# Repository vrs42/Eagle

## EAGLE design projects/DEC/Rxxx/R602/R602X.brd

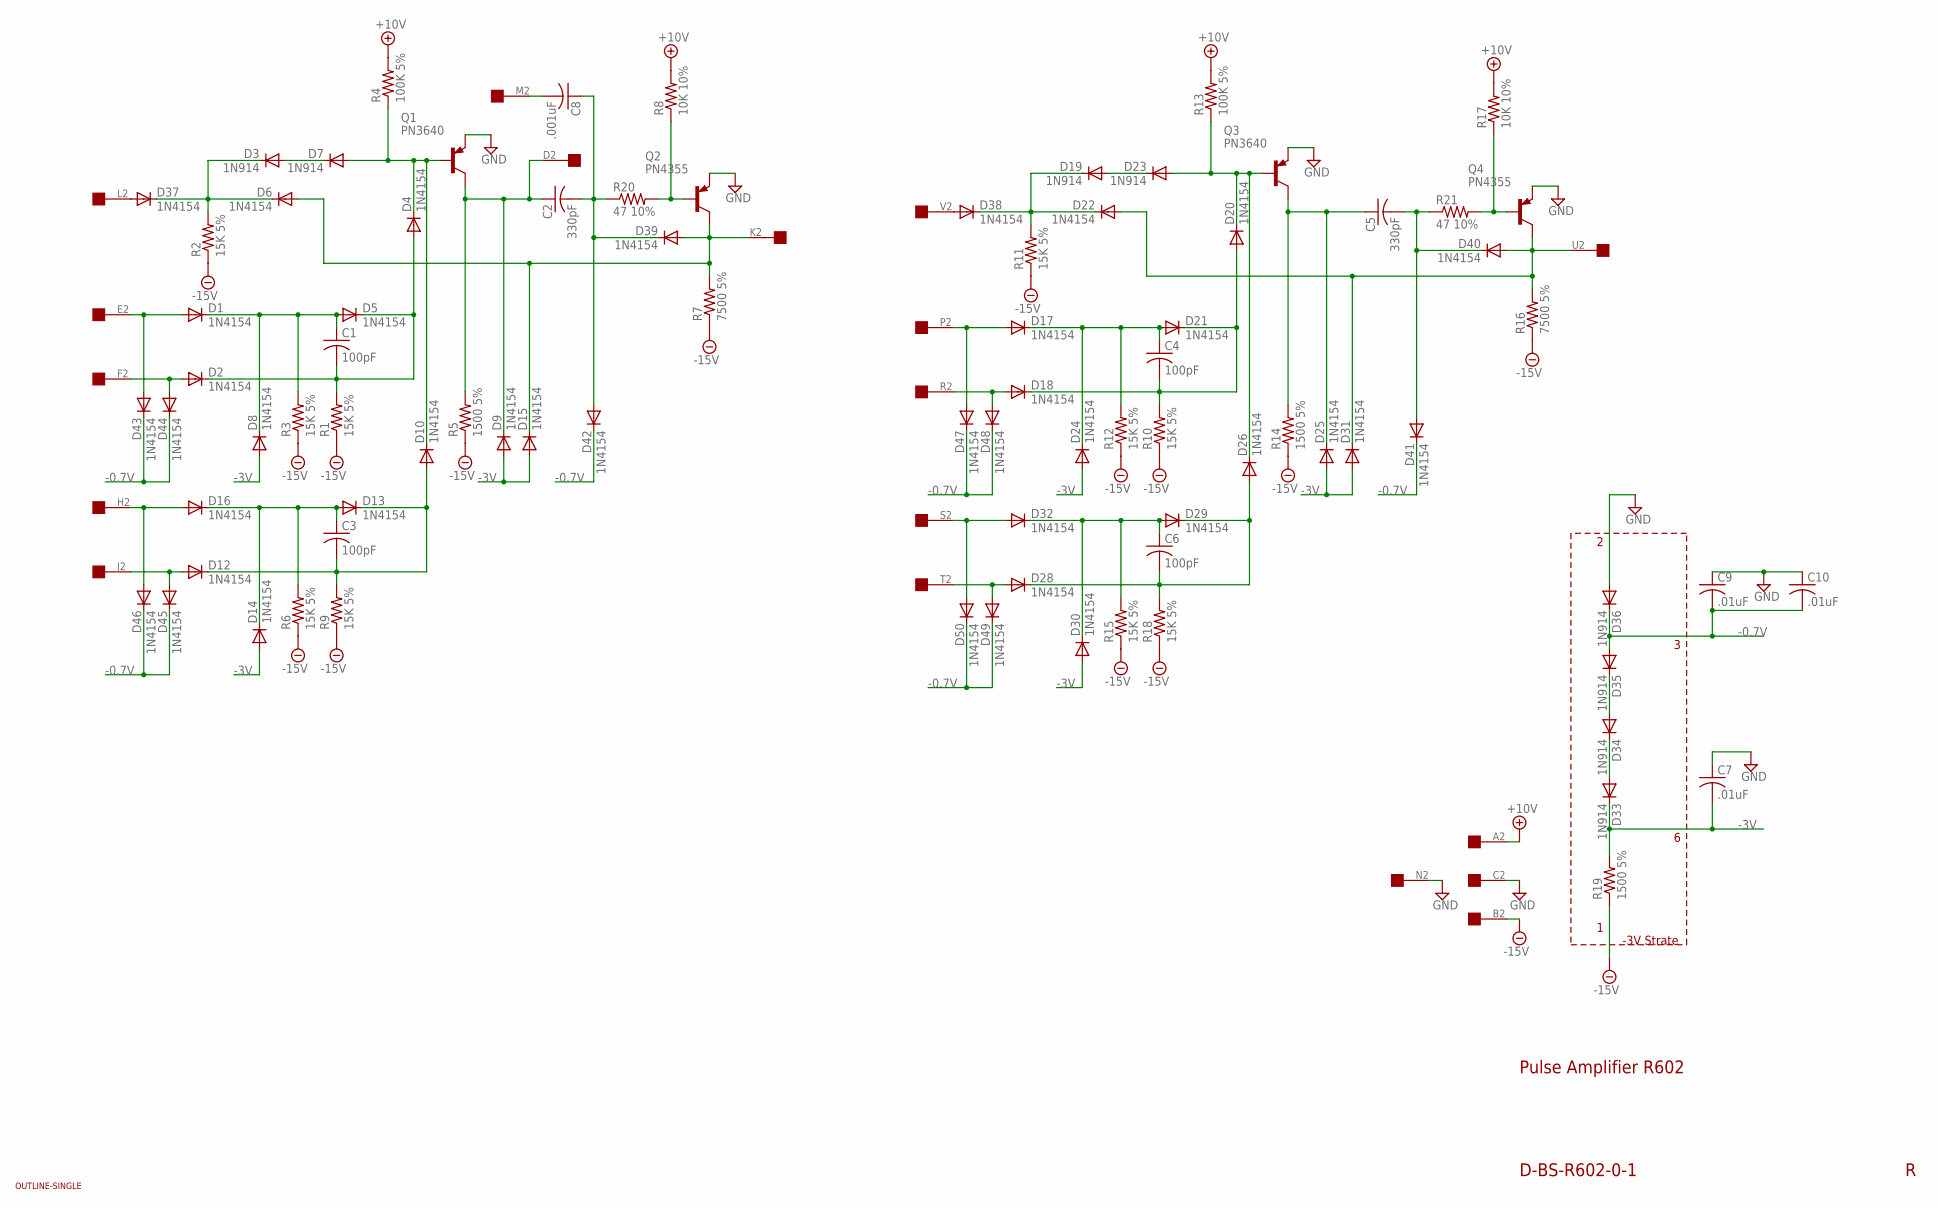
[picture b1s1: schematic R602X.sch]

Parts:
C1, C3, C4, C6: 100pF; C050-025X075
C2, C5: 330pF; C050-025X075
C7: .01uF; C075-032X103
C8: .001uF; C050-025X075
C9, C10: .01uF; C050-025X075
D1, D2, D4, D5, D6, D8, D9, D10, D12, D13, D14, D15, D16, D17, D18, D20, D21, D22, D24, D25, D26, D28, D29, D30, D31, D32, D37, D38, D39, D40, D41, D42, D43, D44, D45, D46, D47, D48, D49, D50: 1N4154; DO35-10
D3, D7, D19, D23, D33, D34, D35, D36: 1N914; DO35-10
Q1, Q3: PN3640; TO39
Q2, Q4: PN4355; TO39
R1, R2, R3, R6, R9, R10, R11, R12, R15, R18: 15K 5%; 0207/10
R4, R13: 100K 5%; 0207/10
R5, R14, R19: 1500 5%; 0207/10
R7, R16: 7500 5%; 0207/10
R8, R17: 10K 10%; 0207/10
R20, R21: 47 10%; 0207/10
U$1: OUTLINE-SINGLE; SINGLE
U$2: EDGE-1; EDGE-CON1

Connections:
+10V: R4.2, R8.2, R13.2, R17.2, U$2.A2
-0.7V: C9.2, C10.2, D35.A, D36.C, D41.C, D42.C, D43.C, D44.C, D45.C, D46.C, D47.C, D48.C, D49.C, D50.C
-3V: C7.2, D8.A, D9.A, D14.A, D15.A, D24.A, D25.A, D30.A, D31.A, D33.C, R19.2
-15V: R1.1, R2.1, R3.1, R5.1, R6.1, R7.1, R9.1, R10.1, R11.1, R12.1, R14.1, R15.1, R16.1, R18.1, R19.1, U$2.B2
GND: C7.1, C9.1, C10.1, D36.A, Q1.1 (E), Q2.1 (E), Q3.1 (E), Q4.1 (E), U$2.C2, U$2.N2
unnamed: D37.A, U$2.L2
unnamed: D3.C, D6.C, D37.C, R2.2
unnamed: D1.A, D43.A, U$2.E2
unnamed: D2.A, D44.A, U$2.F2
unnamed: C1.1, D1.C, D5.A, D8.C, R3.2
unnamed: C1.2, D2.C, D4.A, D5.C, R1.2
unnamed: D3.A, D7.C
unnamed: D34.A, D35.C
unnamed: D33.A, D34.C
unnamed: D4.C, D7.A, D10.C, Q1.2 (B), R4.1
unnamed: C2.1, D9.C, Q1.3 (C), R5.2, U$2.D2
unnamed: C2.2, C8.1, D39.C, D42.A, R20.1
unnamed: Q2.2 (B), R8.1, R20.2
unnamed: D6.A, D15.C, D39.A, Q2.3 (C), R7.2, U$2.K2
unnamed: D16.A, D46.A, U$2.H2
unnamed: D12.A, D45.A, U$2.J2
unnamed: C3.1, D13.A, D14.C, D16.C, R6.2
unnamed: C3.2, D10.A, D12.C, D13.C, R9.2
unnamed: D17.A, D47.A, U$2.P2
unnamed: D18.A, D48.A, U$2.R2
unnamed: C4.1, D17.C, D21.A, D24.C, R12.2
unnamed: C4.2, D18.C, D20.A, D21.C, R10.2
unnamed: D38.A, U$2.V2
unnamed: D19.C, D22.C, D38.C, R11.2
unnamed: D19.A, D23.C
unnamed: D20.C, D23.A, D26.C, Q3.2 (B), R13.1
unnamed: C5.1, D25.C, Q3.3 (C), R14.2
unnamed: C5.2, D40.C, D41.A, R21.1
unnamed: Q4.2 (B), R17.1, R21.2
unnamed: D22.A, D31.C, D40.A, Q4.3 (C), R16.2, U$2.U2
unnamed: D32.A, D50.A, U$2.S2
unnamed: D28.A, D49.A, U$2.T2
unnamed: C6.1, D29.A, D30.C, D32.C, R15.2
unnamed: C6.2, D26.A, D28.C, D29.C, R18.2
unnamed: C8.2, U$2.M2

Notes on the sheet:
Pulse Amplifier R602
D-BS-R602-0-1
-3V Strate

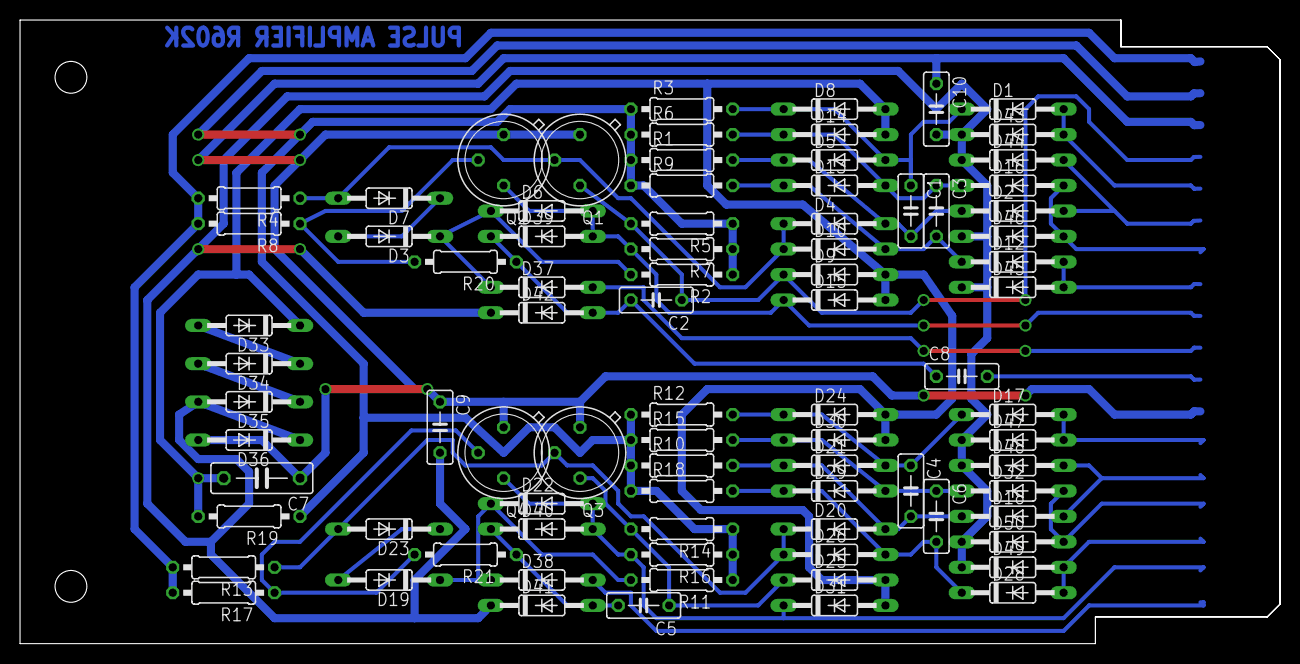
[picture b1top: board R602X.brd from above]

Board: 2 copper layers, 125.7 x 62.2 mm, 85 parts (0 on the bottom side), 40 nets.

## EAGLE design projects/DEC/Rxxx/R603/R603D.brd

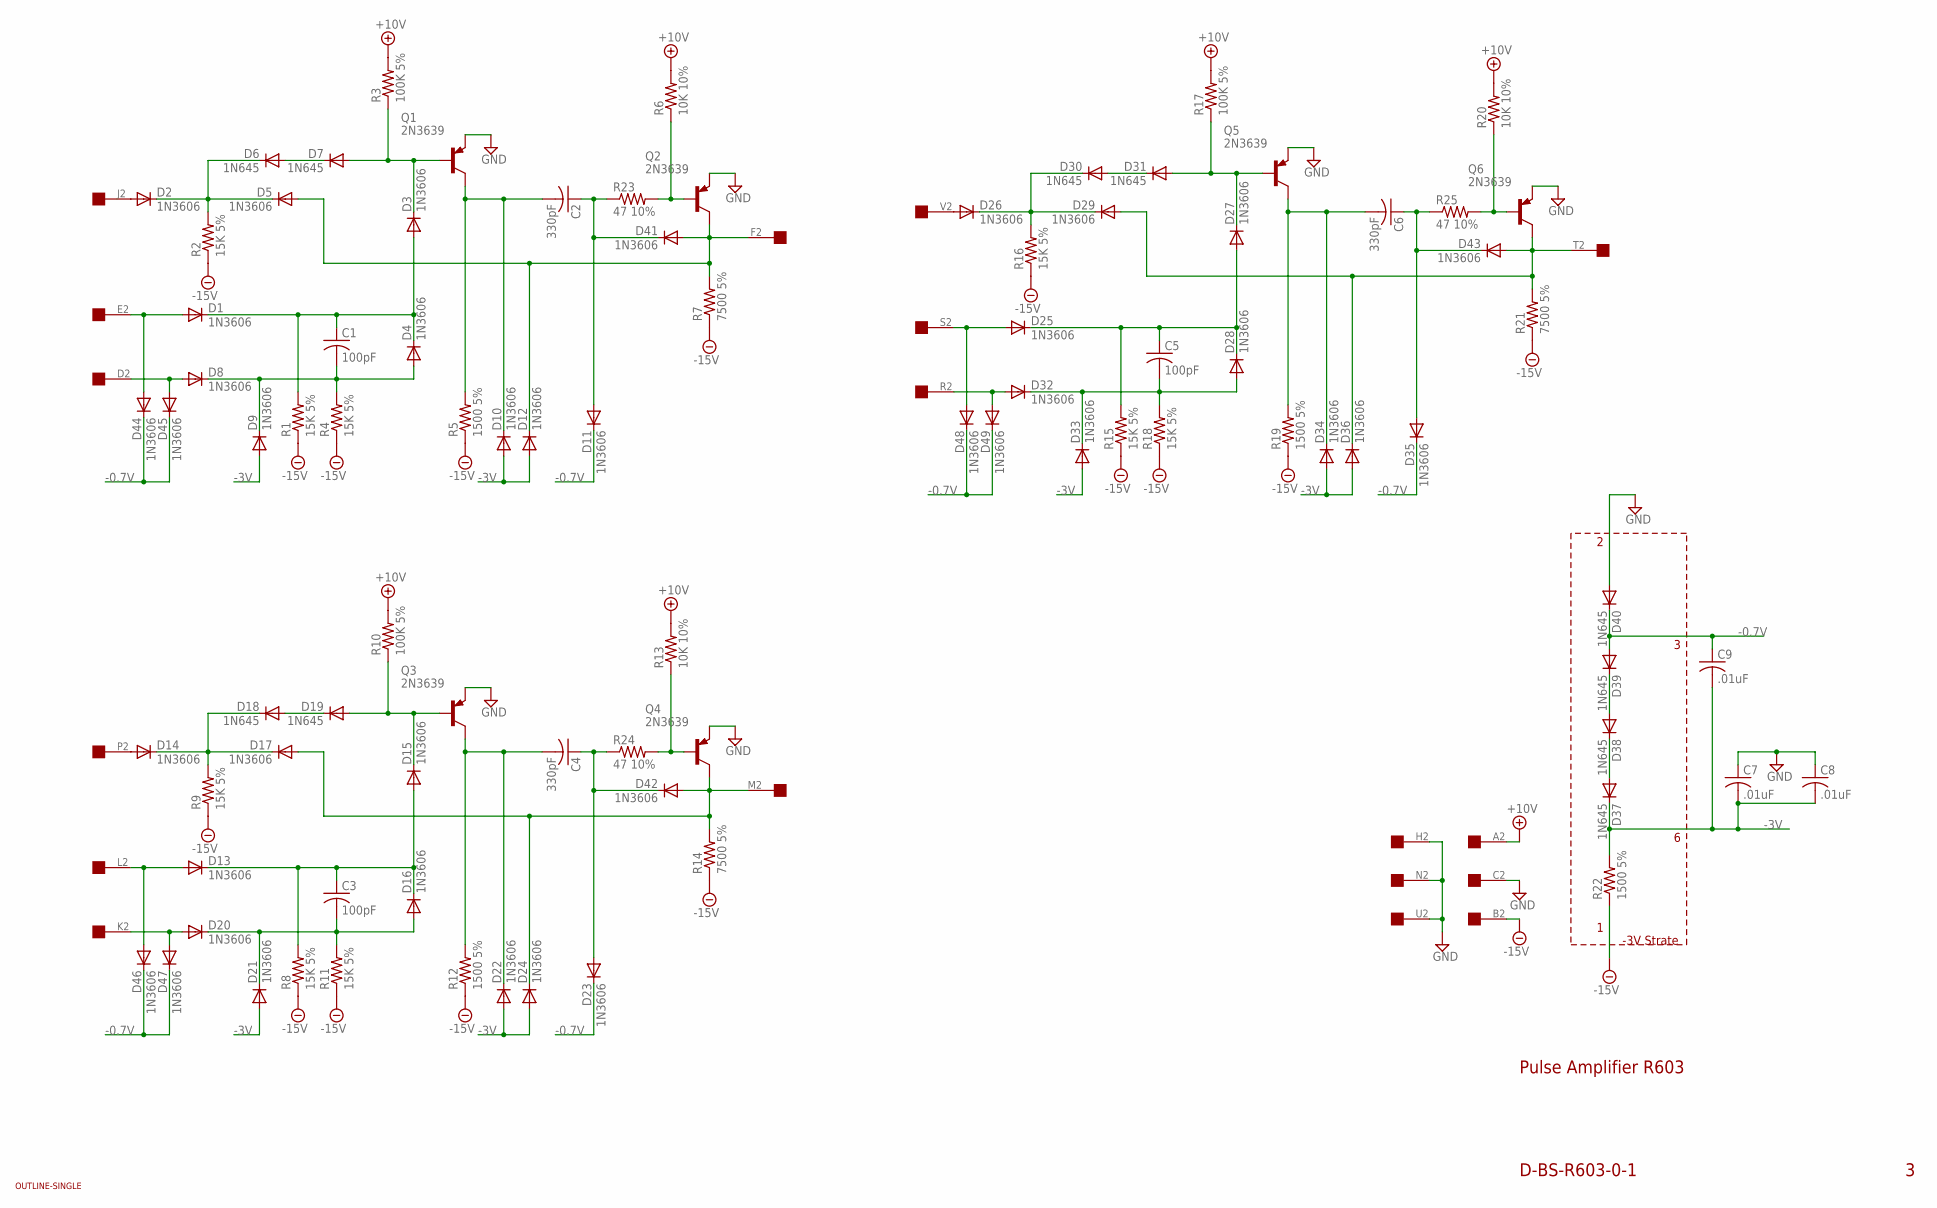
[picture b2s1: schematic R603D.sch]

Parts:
C1, C3, C5: 100pF; C050-025X075
C2, C4, C6: 330pF; C050-025X075
C7, C8, C9: .01uF; C050-025X075
D1, D2, D3, D4, D5, D8, D9, D10, D11, D12, D13, D14, D15, D16, D17, D20, D21, D22, D23, D24, D25, D26, D27, D28, D29, D32, D33, D34, D35, D36, D41, D42, D43, D44, D45, D46, D47, D48, D49: 1N3606; DO35-10
D6, D7, D18, D19, D30, D31, D37, D38, D39, D40: 1N645; DO35-10
Q1, Q2, Q3, Q4, Q5, Q6: 2N3639; TO39
R1, R2, R4, R8, R9, R11, R15, R16, R18: 15K 5%; 0207/10
R3, R10, R17: 100K 5%; 0207/10
R5, R12, R19, R22: 1500 5%; 0207/10
R6, R13, R20: 10K 10%; 0207/10
R7, R14, R21: 7500 5%; 0207/10
R23, R24, R25: 47 10%; 0207/10
U$1: OUTLINE-SINGLE; SINGLE
U$2: EDGE-1; EDGE-CON1

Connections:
+10V: R3.2, R6.2, R10.2, R13.2, R17.2, R20.2, U$2.A2
-0.7V: C9.1, D11.C, D23.C, D35.C, D39.A, D40.C, D44.C, D45.C, D46.C, D47.C, D48.C, D49.C
-3V: C7.2, C8.2, C9.2, D9.A, D10.A, D12.A, D21.A, D22.A, D24.A, D33.A, D34.A, D36.A, D37.C, R22.2
-15V: R1.1, R2.1, R4.1, R5.1, R7.1, R8.1, R9.1, R11.1, R12.1, R14.1, R15.1, R16.1, R18.1, R19.1, R21.1, R22.1, U$2.B2
GND: C7.1, C8.1, D40.A, Q1.1 (E), Q2.1 (E), Q3.1 (E), Q4.1 (E), Q5.1 (E), Q6.1 (E), U$2.C2, U$2.H2, U$2.N2, U$2.U2
unnamed: D2.A, U$2.J2
unnamed: D2.C, D5.C, D6.C, R2.2
unnamed: D1.A, D44.A, U$2.E2
unnamed: D8.A, D45.A, U$2.D2
unnamed: C1.1, D1.C, D3.A, D4.C, R1.2
unnamed: C1.2, D4.A, D8.C, D9.C, R4.2
unnamed: D6.A, D7.C
unnamed: D38.A, D39.C
unnamed: D37.A, D38.C
unnamed: D3.C, D7.A, Q1.2 (B), R3.1
unnamed: C2.2, D10.C, Q1.3 (C), R5.2
unnamed: C2.1, D11.A, D41.C, R23.1
unnamed: Q2.2 (B), R6.1, R23.2
unnamed: D5.A, D12.C, D41.A, Q2.3 (C), R7.2, U$2.F2
unnamed: D13.A, D46.A, U$2.L2
unnamed: D20.A, D47.A, U$2.K2
unnamed: C3.1, D13.C, D15.A, D16.C, R8.2
unnamed: C3.2, D16.A, D20.C, D21.C, R11.2
unnamed: D25.A, D48.A, U$2.S2
unnamed: D32.A, D49.A, U$2.R2
unnamed: C5.1, D25.C, D27.A, D28.C, R15.2
unnamed: C5.2, D28.A, D32.C, D33.C, R18.2
unnamed: D26.A, U$2.V2
unnamed: D26.C, D29.C, D30.C, R16.2
unnamed: D30.A, D31.C
unnamed: D27.C, D31.A, Q5.2 (B), R17.1
unnamed: C6.2, D34.C, Q5.3 (C), R19.2
unnamed: C6.1, D35.A, D43.C, R25.1
unnamed: Q6.2 (B), R20.1, R25.2
unnamed: D29.A, D36.C, D43.A, Q6.3 (C), R21.2, U$2.T2
unnamed: D14.A, U$2.P2
unnamed: D14.C, D17.C, D18.C, R9.2
unnamed: D18.A, D19.C
unnamed: D15.C, D19.A, Q3.2 (B), R10.1
unnamed: C4.2, D22.C, Q3.3 (C), R12.2
unnamed: C4.1, D23.A, D42.C, R24.1
unnamed: Q4.2 (B), R13.1, R24.2
unnamed: D17.A, D24.C, D42.A, Q4.3 (C), R14.2, U$2.M2

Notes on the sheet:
Pulse Amplifier R603
D-BS-R603-0-1
-3V Strate

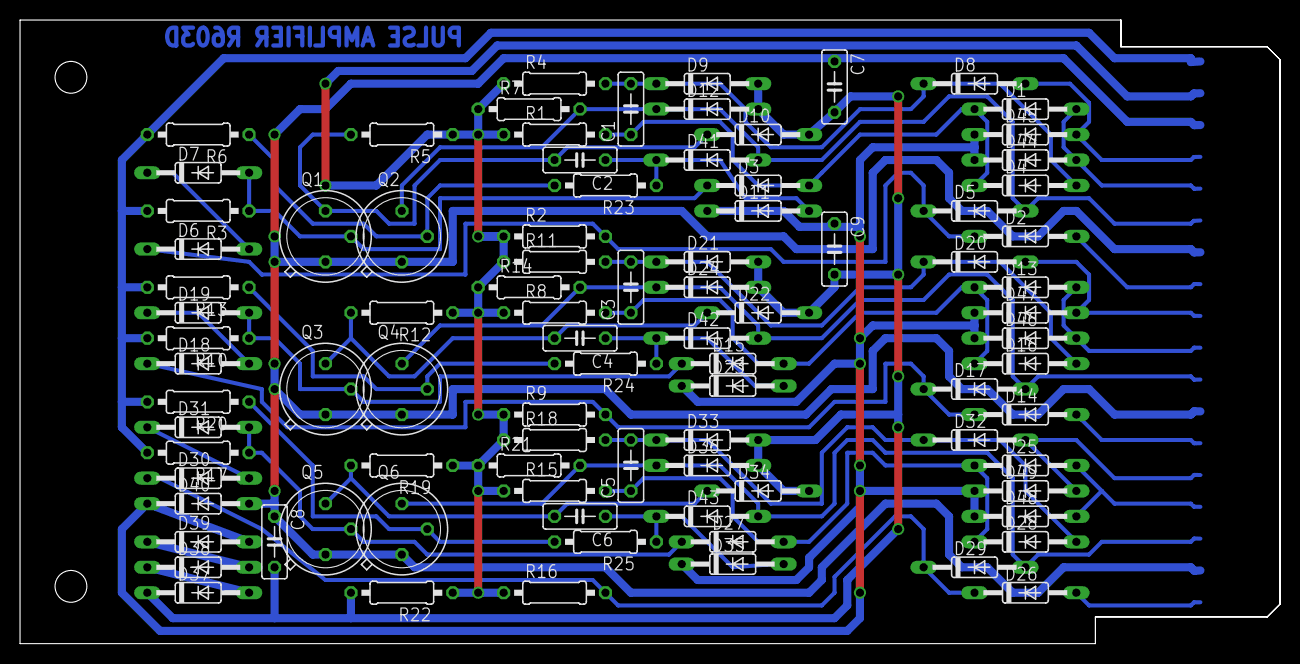
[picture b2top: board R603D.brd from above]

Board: 2 copper layers, 125.7 x 62.2 mm, 91 parts (0 on the bottom side), 43 nets.

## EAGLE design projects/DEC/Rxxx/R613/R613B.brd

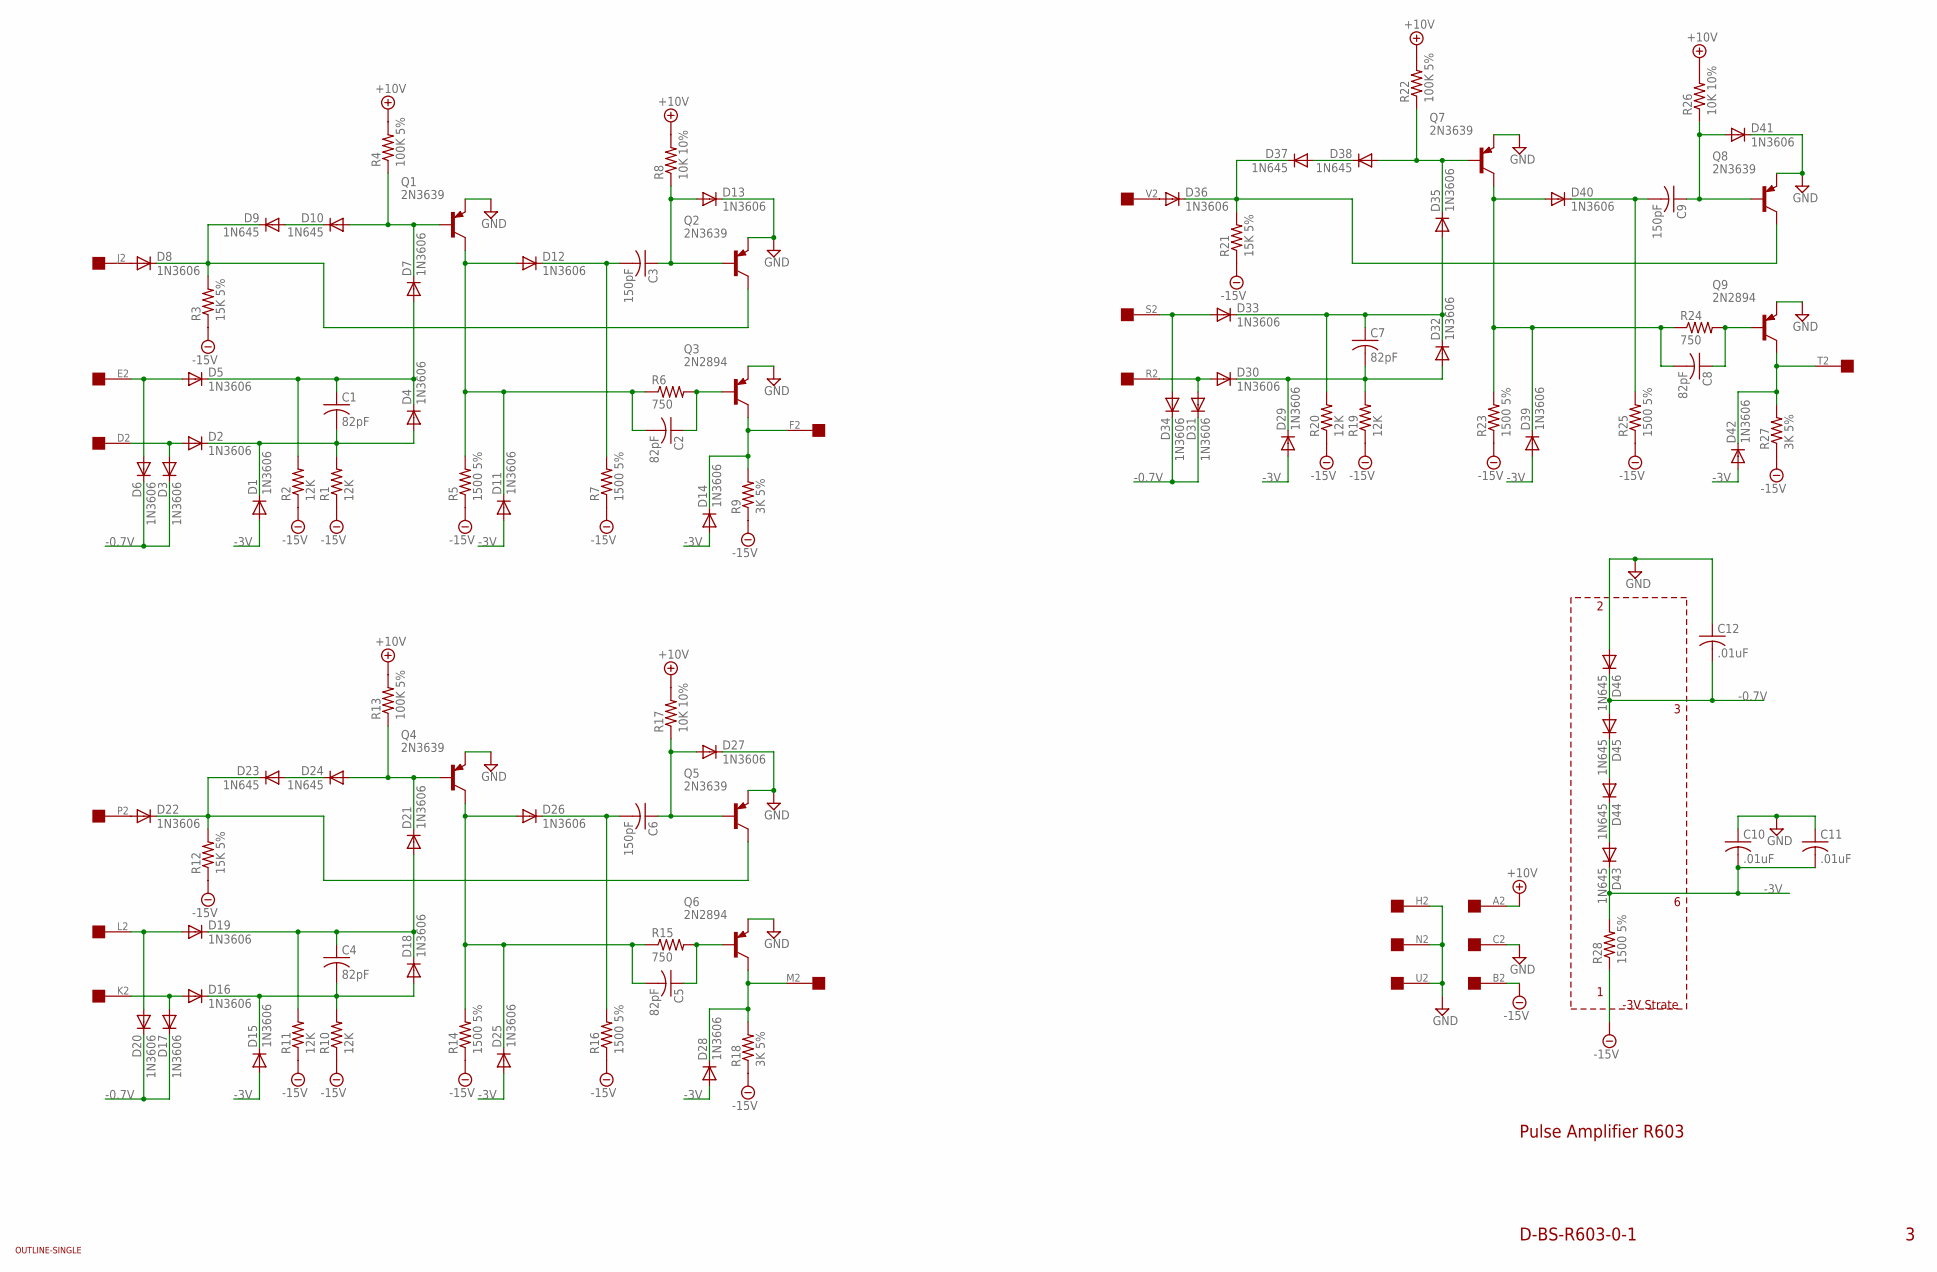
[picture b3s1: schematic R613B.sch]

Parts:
C1, C2, C4, C5, C7, C8: 82pF; C050-025X075
C3, C6, C9: 150pF; C050-025X075
C10, C11, C12: .01uF; C050-025X075
D1, D2, D3, D4, D5, D6, D7, D8, D11, D12, D13, D14, D15, D16, D17, D18, D19, D20, D21, D22, D25, D26, D27, D28, D29, D30, D31, D32, D33, D34, D35, D36, D39, D40, D41, D42: 1N3606; DO35-10
D9, D10, D23, D24, D37, D38, D43, D44, D45, D46: 1N645; DO35-10
Q1, Q2, Q4, Q5, Q7, Q8: 2N3639; TO39
Q3, Q6, Q9: 2N2894; TO39
R1, R2, R10, R11, R19, R20: 12K; 0207/10
R3, R12, R21: 15K 5%; 0207/10
R4, R13, R22: 100K 5%; 0207/10
R5, R7, R14, R16, R23, R25, R28: 1500 5%; 0207/10
R6, R15, R24: 750; 0207/10
R8, R17, R26: 10K 10%; 0207/10
R9, R18, R27: 3K 5%; 0207/10
U$1: OUTLINE-SINGLE; SINGLE
U$2: EDGE-1; EDGE-CON1

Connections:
+10V: R4.2, R8.2, R13.2, R17.2, R22.2, R26.2, U$2.A2
-0.7V: C12.2, D3.C, D6.C, D17.C, D20.C, D31.C, D34.C, D45.A, D46.C
-3V: C10.2, C11.2, D1.A, D11.A, D14.A, D15.A, D25.A, D28.A, D29.A, D39.A, D42.A, D43.C, R28.2
-15V: R1.1, R2.1, R3.1, R5.1, R7.1, R9.1, R10.1, R11.1, R12.1, R14.1, R16.1, R18.1, R19.1, R20.1, R21.1, R23.1, R25.1, R27.1, R28.1, U$2.B2
GND: C10.1, C11.1, C12.1, D13.C, D27.C, D41.C, D46.A, Q1.1 (E), Q2.1 (E), Q3.1 (E), Q4.1 (E), Q5.1 (E), Q6.1 (E), Q7.1 (E), Q8.1 (E), Q9.1 (E), U$2.C2, U$2.H2, U$2.N2, U$2.U2
unnamed: D8.A, U$2.J2
unnamed: D8.C, D9.C, Q2.3 (C), R3.2
unnamed: D5.A, D6.A, U$2.E2
unnamed: D2.A, D3.A, U$2.D2
unnamed: C1.1, D4.C, D5.C, D7.A, R2.2
unnamed: C1.2, D1.C, D2.C, D4.A, R1.2
unnamed: D9.A, D10.C
unnamed: D44.A, D45.C
unnamed: D43.A, D44.C
unnamed: D7.C, D10.A, Q1.2 (B), R4.1
unnamed: C2.2, D11.C, D12.A, Q1.3 (C), R5.2, R6.1
unnamed: C3.2, D12.C, R7.2
unnamed: C3.1, D13.A, Q2.2 (B), R8.1
unnamed: D14.C, Q3.3 (C), R9.2, U$2.F2
unnamed: D19.A, D20.A, U$2.L2
unnamed: D16.A, D17.A, U$2.K2
unnamed: C4.1, D18.C, D19.C, D21.A, R11.2
unnamed: C4.2, D15.C, D16.C, D18.A, R10.2
unnamed: D33.A, D34.A, U$2.S2
unnamed: D30.A, D31.A, U$2.R2
unnamed: C7.1, D32.C, D33.C, D35.A, R20.2
unnamed: C7.2, D29.C, D30.C, D32.A, R19.2
unnamed: D36.A, U$2.V2
unnamed: D36.C, D37.C, Q8.3 (C), R21.2
unnamed: D37.A, D38.C
unnamed: D35.C, D38.A, Q7.2 (B), R22.1
unnamed: D22.C, D23.C, Q5.3 (C), R12.2
unnamed: D28.C, Q6.3 (C), R18.2, U$2.M2
unnamed: C5.1, Q6.2 (B), R15.2
unnamed: C5.2, D25.C, D26.A, Q4.3 (C), R14.2, R15.1
unnamed: D22.A, U$2.P2
unnamed: D23.A, D24.C
unnamed: D21.C, D24.A, Q4.2 (B), R13.1
unnamed: C6.2, D26.C, R16.2
unnamed: C8.2, D39.C, D40.A, Q7.3 (C), R23.2, R24.1
unnamed: C6.1, D27.A, Q5.2 (B), R17.1
unnamed: C2.1, Q3.2 (B), R6.2
unnamed: D42.C, Q9.3 (C), R27.2, U$2.T2
unnamed: C8.1, Q9.2 (B), R24.2
unnamed: C9.2, D40.C, R25.2
unnamed: C9.1, D41.A, Q8.2 (B), R26.1

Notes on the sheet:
Pulse Amplifier R603
D-BS-R603-0-1
-3V Strate

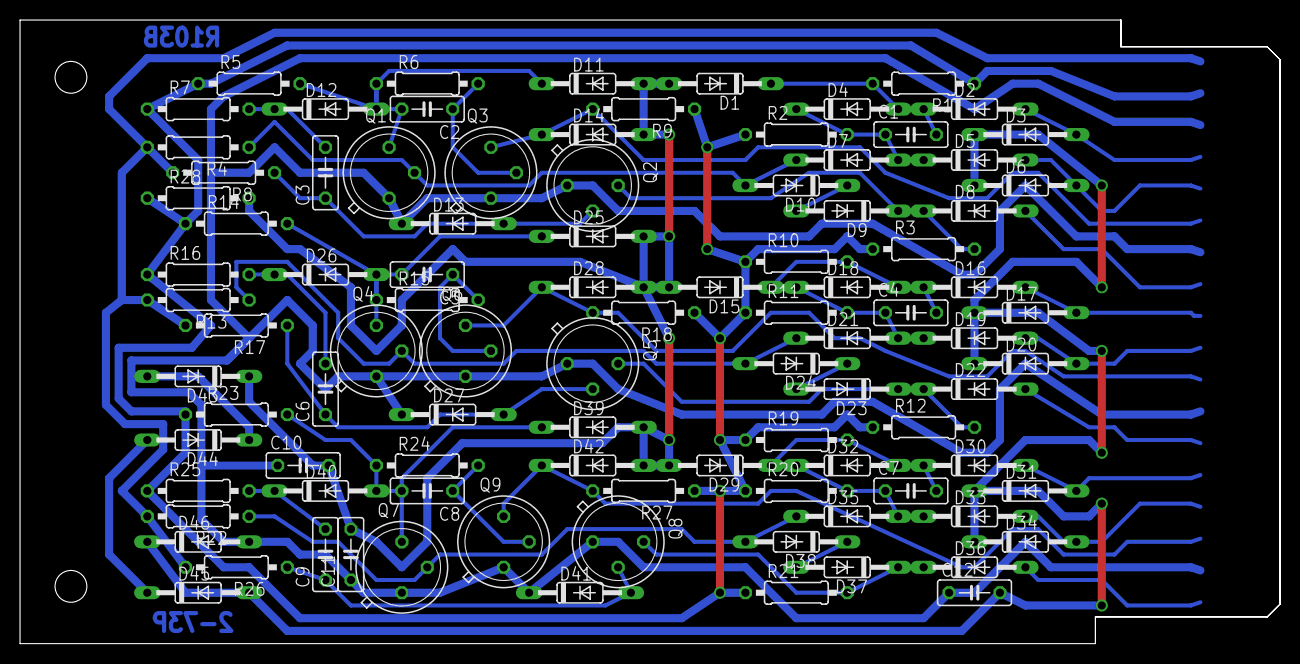
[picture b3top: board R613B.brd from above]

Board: 2 copper layers, 125.7 x 62.2 mm, 97 parts (0 on the bottom side), 46 nets.

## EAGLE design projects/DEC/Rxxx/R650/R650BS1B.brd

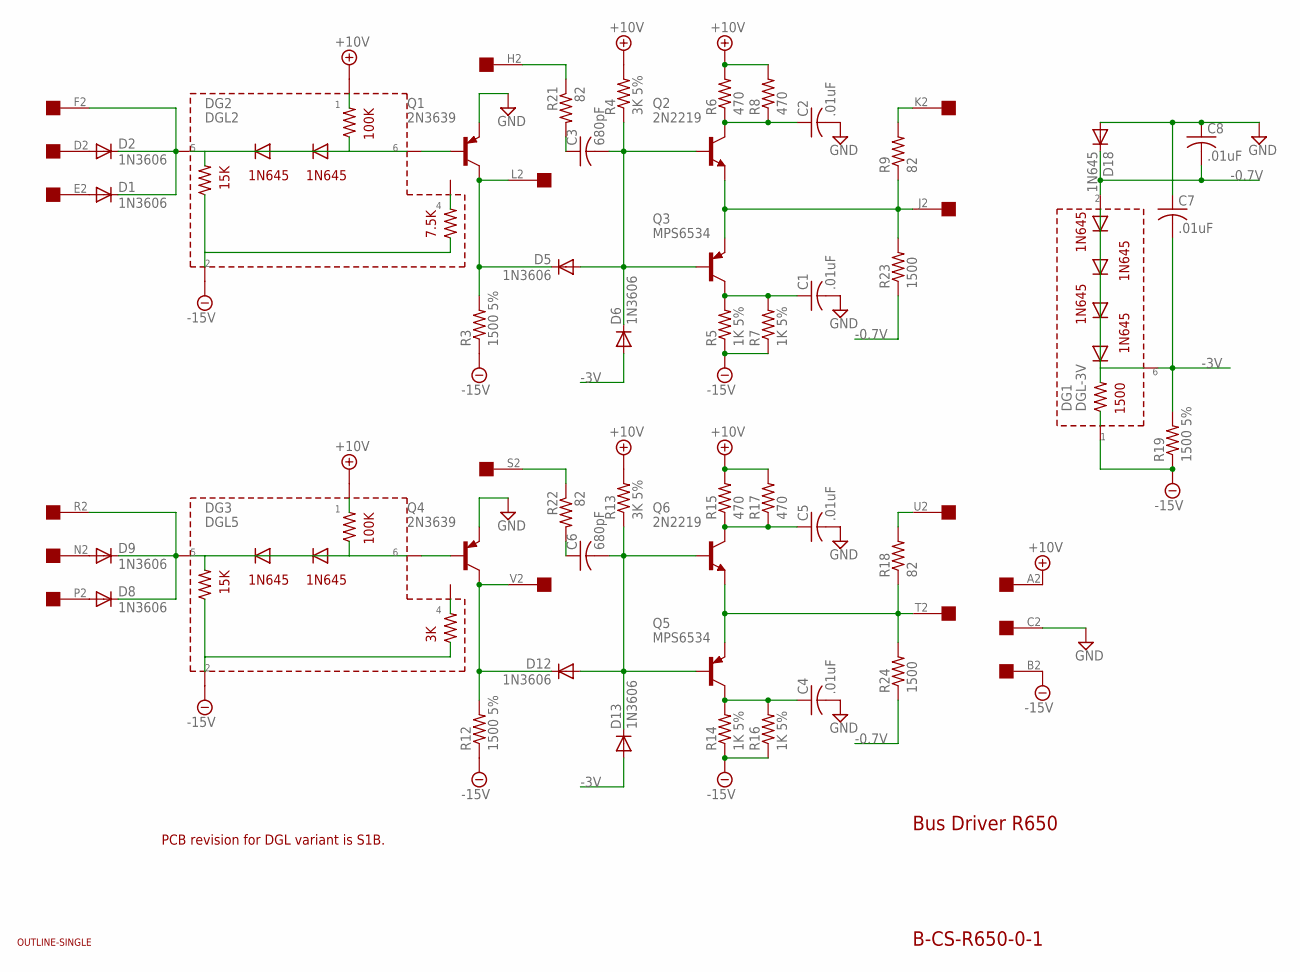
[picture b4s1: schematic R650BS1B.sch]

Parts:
C1, C2, C4, C5, C7, C8: .01uF; C102-043X133
C3, C6: 680pF; C102-043X133
D1, D2, D5, D6, D8, D9, D12, D13: 1N3606; DO35-10
D18: 1N645; DO35-10
DG1: DGL-3V; DGL2
DG2: DGL2
DG3: DGL5; DGL2
Q1, Q4: 2N3639; TO39
Q2, Q6: 2N2219; TO5
Q3, Q5: MPS6534; TO39
R3, R12, R19: 1500 5%; 0207/10
R4, R13: 3K 5%; 0207/10
R5, R7, R14, R16: 1K 5%; 0207/10
R6, R8, R15, R17: 470; 0207/10
R9, R18, R21, R22: 82; 0207/10
R23, R24: 1500; 0207/10
U$1: OUTLINE-SINGLE; SINGLE
U$2: EDGE-1; EDGE-CON1

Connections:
+10V: DG2.P$1 (1), DG3.P$1 (1), R4.2, R6.2, R8.2, R13.2, R15.2, R17.2, U$2.A2
-0.7V: C8.2, D18.C, DG1.P$2 (2), R23.1, R24.1
-3V: C7.2, D6.A, D13.A, DG1.P$6 (6), R19.2
-15V: DG1.P$1 (1), DG2.P$2 (2), DG3.P$2 (2), R3.1, R5.1, R7.1, R12.1, R14.1, R16.1, R19.1, U$2.B2
GND: C1.2, C2.2, C4.2, C5.2, C7.1, C8.1, D18.A, Q1.1 (E), Q4.1 (E), U$2.C2
unnamed: C3.2, D5.A, D6.C, Q2.2 (B), Q3.2 (B), R4.1
unnamed: Q2.1 (E), Q3.1 (E), R9.1, R23.2, U$2.J2
unnamed: R9.2, U$2.K2
unnamed: D12.C, Q4.3 (C), R12.2, U$2.V2
unnamed: D5.C, Q1.3 (C), R3.2, U$2.L2
unnamed: C2.1, Q2.3 (C), R6.1, R8.1
unnamed: C1.1, Q3.3 (C), R5.2, R7.2
unnamed: DG2.P$6 (6), Q1.2 (B)
unnamed: DG3.P$6 (6), Q4.2 (B)
unnamed: D8.C, D9.C, DG3.P$5 (5), U$2.R2
unnamed: R21.1, U$2.H2
unnamed: C3.1, R21.2
unnamed: C6.2, D12.A, D13.C, Q5.2 (B), Q6.2 (B), R13.1
unnamed: Q5.1 (E), Q6.1 (E), R18.1, R24.2, U$2.T2
unnamed: D1.A, U$2.E2
unnamed: D1.C, D2.C, DG2.P$5 (5), U$2.F2
unnamed: C5.1, Q6.3 (C), R15.1, R17.1
unnamed: C4.1, Q5.3 (C), R14.2, R16.2
unnamed: R18.2, U$2.U2
unnamed: R22.1, U$2.S2
unnamed: C6.1, R22.2
unnamed: D9.A, U$2.N2
unnamed: D8.A, U$2.P2
unnamed: D2.A, U$2.D2

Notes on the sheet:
Bus Driver R650
B-CS-R650-0-1
PCB revision for DGL variant is S1B.

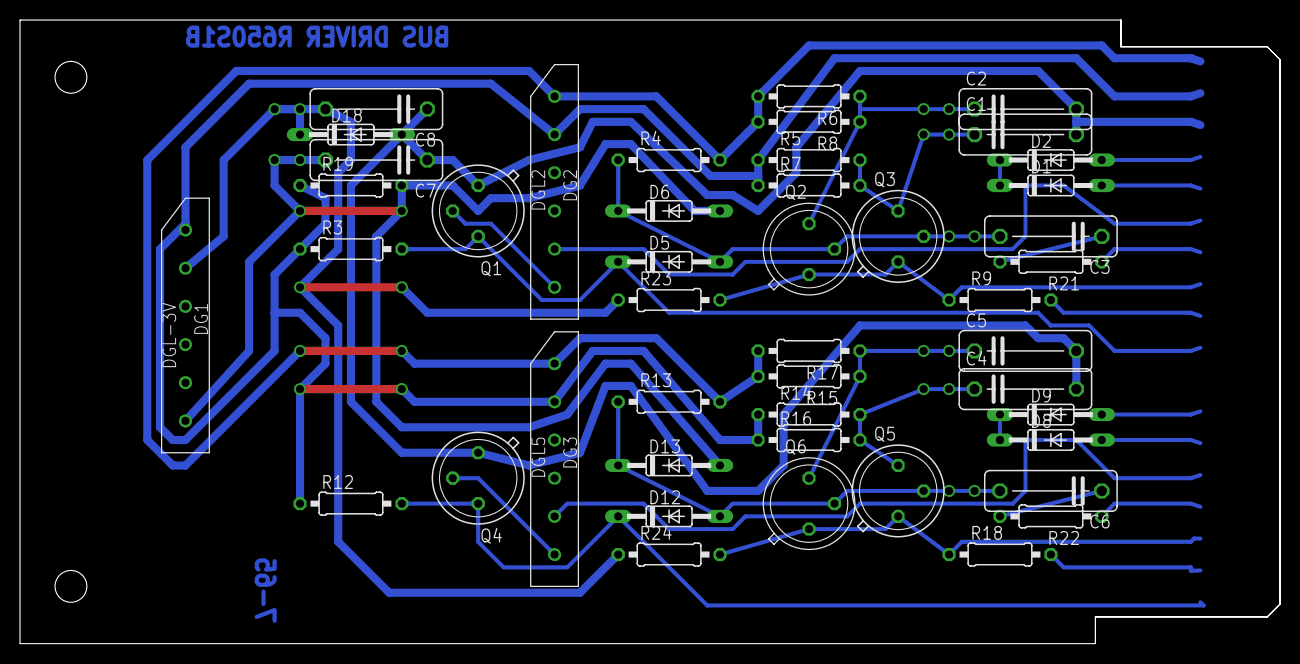
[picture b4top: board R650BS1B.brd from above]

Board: 2 copper layers, 125.7 x 62.2 mm, 47 parts (0 on the bottom side), 29 nets.
